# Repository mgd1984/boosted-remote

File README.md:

# Boosted Remote Reverse-Engineering Starter

This repo contains a first-pass reverse-engineered hardware recreation of the Boosted Boards thumbwheel remote:

- a Blender-generated enclosure
- a KiCad schematic
- a KiCad PCB
- documented assumptions tying the mechanical and electrical work back to source material

This is not a firmware-complete clone. The hardware is designed to match the known control architecture and packaging constraints while using currently accessible parts and a reproducible scripted workflow.

## Source Anchors

- Boosted USA product page for the later thumbwheel remote exterior reference:
  - <https://boostedusa.com/products/boosted-remote>
- Beam Break BLE reverse-engineering notes confirming later remote BLE behavior and pairing model:
  - <https://beambreak.org/articles/remote_ble_ids/>
- XR General Hospital replacement PCBA product confirming that a retrofit board in the original enclosure is practical:
  - <https://www.xrgeneralhospital.com/beta/p/remote-controller-pcba>

## Generated Assets

- Active enclosure blend: `outputs/blender/boosted_remote_enclosure.blend`
- Active PCB review blend: `outputs/blender/boosted_remote_pcb_all_layers.blend`
- Build123d CAD package: `mechanical/cad/`
- Build123d generator CLI: `mechanical/scripts/build_enclosure.py`
- Proxy-section extractor: `mechanical/scripts/analyze_proxy_glb.py`
- KiCad project: `electrical/kicad/boosted_remote.kicad_pro`
- Live board and schematic: `electrical/kicad/boosted_remote.kicad_pcb`, `electrical/kicad/boosted_remote.kicad_sch`
- Routing packet script: `electrical/scripts/route_packets.py`
- Netclass configurator: `electrical/scripts/configure_netclasses.py`
- Blender export path: `electrical/scripts/export_kicad_to_blender.py`
- Shared parameters: `config/remote_params.json`
- Reverse-engineering notes: `docs/reverse_engineering_notes.md`
- Build123d pipeline notes: `docs/build123d_enclosure.md`
- Repo navigation map: `docs/repo_map.md`

## Where To Work Now

- Mechanical source of truth: `mechanical/cad/`
- Generated Blender outputs: `outputs/blender/`
- Mechanical build entry point: `mechanical/scripts/build_enclosure.py`
- Shared parameter contract: `config/remote_params.json`
- Active KiCad project: `electrical/kicad/boosted_remote.kicad_pro`
- Active board and schematic: `electrical/kicad/boosted_remote.kicad_pcb`, `electrical/kicad/boosted_remote.kicad_sch`
- Electrical utilities and routing helpers: `electrical/scripts/`
- Mechanical utilities: `mechanical/scripts/`
- Historical electrical scripts: `history/electrical/scripts/`
- Historical mechanical scripts and studies: `history/mechanical/`
- Historical utilities: `history/utilities/`

## Repo Shape

- `electrical/kicad/`: live KiCad project only
- `electrical/scripts/`: active live-board utilities only
- `mechanical/cad/`: code-first enclosure source of truth
- `mechanical/scripts/`: active enclosure utilities only
- `mechanical/references/`: supporting 2D outline reference assets used by the CAD pipeline
- `outputs/`: generated Blender scenes, renders, and scratch outputs
- `history/electrical/`: older routing and migration helpers
- `history/mechanical/`: non-canonical lineage, experiments, displaced scenes, and older scripts
- `history/utilities/`: historical support scripts and geometry probes
- `config/`: shared project configuration and parameter contracts
- `docs/`: workflow notes plus `docs/repo_map.md` for a quick navigation guide

## Current Scope

- Boosted-style ergonomic shell with split enclosure
- thumbwheel opening and internal hall sensor location
- mini-USB charge-port cutout for external visual fidelity
- 1S LiPo power, charger, LDO, BLE MCU, LEDs, buzzer, deadman trigger, programming header
- first-pass PCB shaped to the enclosure cavity
- first-pass build123d enclosure generation for STEP/STL prototype outputs

## Verification Status

- Schematic ERC is down to warnings only on the generated custom-library setup.
- The promoted live PCB checkpoint is:
  - `electrical/kicad/boosted_remote.kicad_pcb`
  - 3 DRC warnings, all silkscreen-only
  - 25 unconnected items remaining
- The live board now includes validated packetized routing improvements over the original generator baseline.
  - Clean promoted packets so far: upper `SW1 -> U4` ground stitch and `PWR_BTN` escape/routing packet
- Experimental routing passes are only promoted when they reduce the open count without introducing blocker DRC categories.

## Known Gaps

- No firmware is included
- Dimensions are inferred and should be validated against a physical remote before fabrication
- The BLE protocol implementation required to pair with an original board is outside this repo
- The trigger and thumbwheel mechanism are mechanically approximated, not metrology-matched

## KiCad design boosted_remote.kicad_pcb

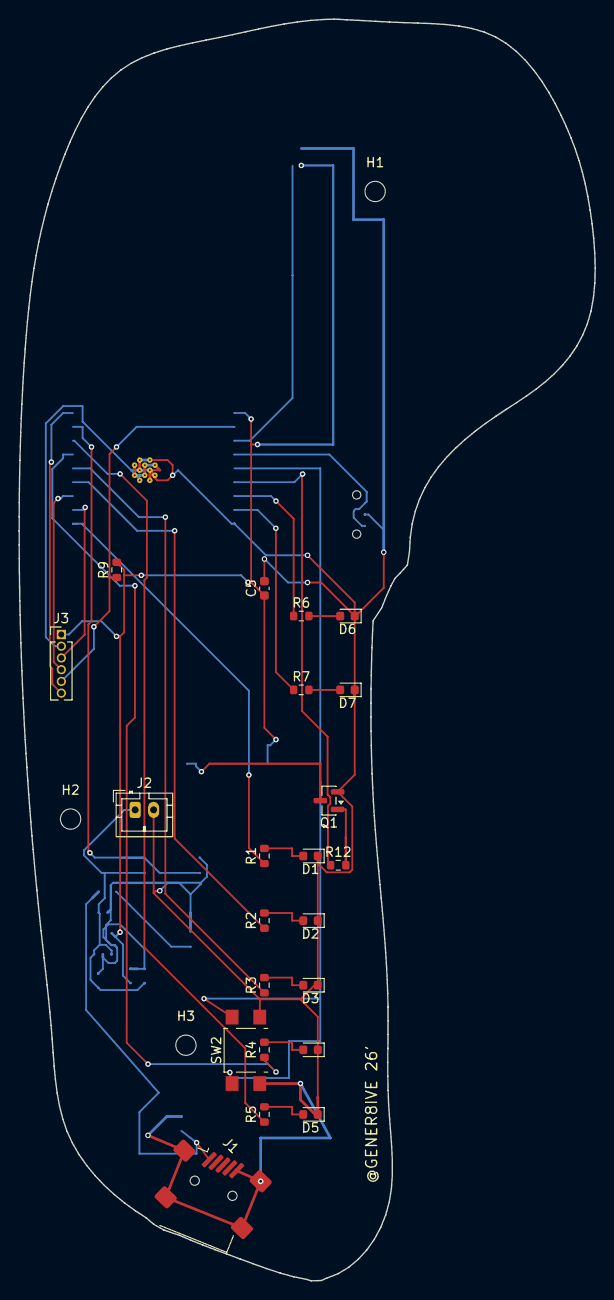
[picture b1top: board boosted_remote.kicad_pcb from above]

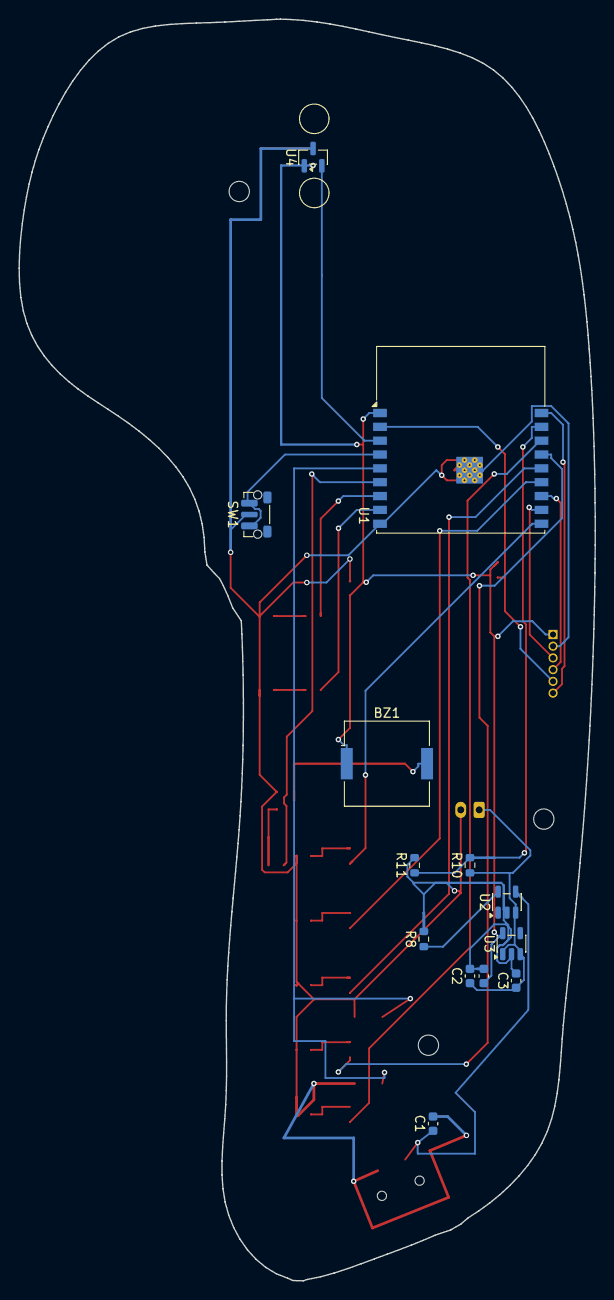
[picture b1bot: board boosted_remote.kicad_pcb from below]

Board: 2 copper layers, 62.4 x 136.7 mm, 38 parts (13 on the bottom side), 30 nets.

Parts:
BZ1: Buzzer; Buzzer_Murata_PKMCS0909E
C1, C2, C4: 4.7u; C_0603_1608Metric
C3: 1u; C_0603_1608Metric
C5: 100n; C_0603_1608Metric
D1, D2, D3, D4, D5: LED; LED_0603_1608Metric
D6: GREEN; LED_0603_1608Metric
D7: BLUE; LED_0603_1608Metric
H1, H2, H3: M2; MountingHole_2.2mm_M2
J1: USB_Mini-B; USB_Mini-B_Lumberg_2486_01_Horizontal
J2: Battery; JST_PH_B2B-PH-K_1x02_P2.00mm_Vertical
J3: UART; PinHeader_1x06_P1.27mm_Vertical
Q1: MMBT3904; SOT-23
R1, R2, R3, R4, R5, R6, R7: 330; R_0603_1608Metric
R8: 4.7k; R_0603_1608Metric
R9: 10k; R_0603_1608Metric
R10: 330k; R_0603_1608Metric
R11: 100k; R_0603_1608Metric
R12: 1k; R_0603_1608Metric
SW1: Deadman; SW_Push_1P1T-MP_NO_Horizontal_Alps_SKRTLAE010
SW2: Power; SW_SPST_TL3305A
U1: ESP32-C3-WROOM-02
U2: MCP73831-2-OT; SOT-23-5
U3: TLV75533PDBV; SOT-23-5
U4: DRV5055A3xDBZxQ1; SOT-23

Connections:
BAT_SENSE: R10.2, R11.1, U1.17
BOOT: J3.6, U1.18
BUZZ: BZ1.2, Q1.3
BUZZ_BASE: Q1.1, R12.2
BUZZ_PWM: R12.1, U1.6
DEADMAN: SW1.1, U1.4
EN: J3.5, R9.1, U1.2
GND: C1.2, C2.2, C3.2, C4.2, C5.2, D1.1, D2.1, D3.1, D4.1, D5.1, D6.1, D7.1, J1.5, J1.SH, J2.2, J3.2, Q1.2, R8.2, R11.2, SW1.2, SW2.2, U1.9, U1.19, U2.2, U3.2, U4.3
HALL_OUT: U1.3, U4.2
LED1: R1.1, U1.10
LED1_A: D1.2, R1.2
LED2: R2.1, U1.13
LED2_A: D2.2, R2.2
LED3: R3.1, U1.14
LED3_A: D3.2, R3.2
LED4: R4.1, U1.15
LED4_A: D4.2, R4.2
LED5: R5.1, U1.16
LED5_A: D5.2, R5.2
PROG: R8.1, U2.5
PWR_BTN: SW2.1, U1.5
STATUS_B: R7.1, U1.8
STATUS_B_A: D7.2, R7.2
STATUS_G: R6.1, U1.7
STATUS_G_A: D6.2, R6.2
UART_RX: J3.3, U1.11
UART_TX: J3.4, U1.12
V3P3: BZ1.1, C4.1, C5.1, J3.1, R9.2, U1.1, U3.5, U4.1
VBAT: C2.1, C3.1, J2.1, R10.1, U2.3, U3.1, U3.3
VBUS: C1.1, J1.1, U2.4

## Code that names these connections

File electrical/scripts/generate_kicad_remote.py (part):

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                PinSpec("2", "VSS", "left"),
                PinSpec("3", "VBAT", "left"),
                PinSpec("4", "VDD", "right"),
                PinSpec("5", "PROG", "right"),
            ],
            15.24,
            12.70,
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        sections.append(obj)
    for obj in label_from_pin(inst["J2"], defs, "2", "GND"):
        sections.append(obj)
    for obj in label_from_pin(inst["J3"], defs, "1", "V3P3"):
        sections.append(obj)
    for obj in label_from_pin(inst["J3"], defs, "2", "GND"):
        sections.append(obj)
    for obj in label_from_pin(inst["J3"], defs, "3", "UART_RX"):
        sections.append(obj)
    for obj in label_from_pin(inst["J3"], defs, "4", "UART_TX"):
        sections.append(obj)
    for obj in label_from_pin(inst["J3"], defs, "5", "EN"):
        sections.append(obj)
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        sections.append(obj)
    for obj in label_from_pin(inst["U3"], defs, "3", "VBAT"):
        sections.append(obj)
    for obj in label_from_pin(inst["U3"], defs, "5", "V3P3"):
        sections.append(obj)
    for obj in label_from_pin(inst["U4"], defs, "1", "V3P3"):
        sections.append(obj)
    for obj in label_from_pin(inst["U4"], defs, "2", "HALL_OUT"):
        sections.append(obj)
    for obj in label_from_pin(inst["U4"], defs, "3", "GND"):
        sections.append(obj)
    for obj in label_from_pin(inst["SW1"], defs, "1", "DEADMAN"):
        sections.append(obj)
    for obj in label_from_pin(inst["SW1"], defs, "2", "GND"):
        sections.append(obj)
    for obj in label_from_pin(inst["SW2"], defs, "1", "PWR_BTN"):
        sections.append(obj)
    for obj in label_from_pin(inst["SW2"], defs, "2", "GND"):
        sections.append(obj)
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    sections.append(wire(71.12, 38.10, 71.12, 43.18))
    sections.append(label("GND", 71.12, 43.18, 90, "left bottom"))
    sections.append(wire(81.28, 113.03, 86.36, 113.03))
    sections.append(label("V3P3", 86.36, 113.03, 180, "right bottom"))
    sections.append(wire(134.62, 116.84, 134.62, 111.76))
    sections.append(label("V3P3", 134.62, 111.76, 270, "right bottom"))
    sections.append(wire(133.35, 76.20, 133.35, 71.12))
    sections.append(label("GND", 133.35, 71.12, 270, "right bottom"))
    sections.append(wire(135.89, 76.20, 135.89, 71.12))
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    sections.append(wire(x_en1, y_en1, x_en1, y_en1 + 5.08))
    sections.append(label("EN", x_en1, y_en1 + 5.08, 90, "left bottom"))
    sections.append(wire(x_en2, y_en2, x_en2, y_en2 - 5.08))
    sections.append(label("V3P3", x_en2, y_en2 - 5.08, 270, "right bottom"))

    # Power capacitors
    for cname, net in (("C1", "VBUS"), ("C2", "VBAT"), ("C3", "VBAT"), ("C4", "V3P3"), ("C5", "V3P3")):
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    midx = (pin_point(inst["R10"], defs, "2")[0] + pin_point(inst["R11"], defs, "1")[0]) / 2.0
    midy = pin_point(inst["R10"], defs, "2")[1]
    sections.append(wire(midx, midy, midx, midy - 5.08))
    sections.append(label("BAT_SENSE", midx, midy - 5.08, 270, "right bottom"))
    sections.append(wire(*pin_point(inst["R11"], defs, "2"), pin_point(inst["R11"], defs, "2")[0], pin_point(inst["R11"], defs, "2")[1] - 5.08))
    sections.append(label("GND", pin_point(inst["R11"], defs, "2")[0], pin_point(inst["R11"], defs, "2")[1] - 5.08, 270, "right bottom"))

    # Buzzer drive
    sections.append(wire(*pin_point(inst["R12"], defs, "1"), pin_point(inst["R12"], defs, "1")[0] - 5.08, pin_point(inst["R12"], defs, "1")[1]))
    sections.append(label("BUZZ_PWM", pin_point(inst["R12"], defs, "1")[0] - 5.08, pin_point(inst["R12"], defs, "1")[1], 0, "left bottom"))
    sections.append(wire(*pin_point(inst["R12"], defs, "2"), *pin_point(inst["Q1"], defs, "1")))
    for obj in label_from_pin(inst["Q1"], defs, "2", "GND"):
        sections.append(obj)
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    sections.append(wire(q1c_x, buzzer_escape_y, bz1n_x, buzzer_escape_y))
    sections.append(wire(bz1n_x, buzzer_escape_y, bz1n_x, bz1n_y))
    sections.append(wire(*pin_point(inst["BZ1"], defs, "1"), pin_point(inst["BZ1"], defs, "1")[0] - 5.08, pin_point(inst["BZ1"], defs, "1")[1]))
    sections.append(label("V3P3", pin_point(inst["BZ1"], defs, "1")[0] - 5.08, pin_point(inst["BZ1"], defs, "1")[1], 0, "left bottom"))

    # LED chains
    led_map = [
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
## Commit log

2026-04-09 Initial repo import
2026-04-09 Remove legacy root board file
2026-04-10 keep mechanical and script cleanup
